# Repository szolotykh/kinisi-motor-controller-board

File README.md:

# Kinisi Motor Controller
For the current **v0.4** hardware, pin mappings, electrical limits and firmware compatibility, see [README_V4.md](README_V4.md). The overview below describes earlier revisions; interface counts and pin assignments differ.

For repeatable Gerber, drill, BOM and placement exports, see
[Regenerating a production package](README_V4.md#regenerating-a-production-package).

Kinisi motor controller is based on STM32F405 microcontroller controller. The controller can control up to 4 brushed DC motors with encoders. It offers platform obstruction which is means user doesn’t need to control each individual motor form main computer, but rather it can control up to four motors as a whole by sending high level commands like set target speed or distance for a platform.

Features:
* Controls 4 motors
* Receives readings from 4 encoders
* Supports encoders with wide range of supply voltage (3.3V, 5V, custom) 

Interfaces:
* USB Serial device
* I2C
* CAN
* 4x GPIO

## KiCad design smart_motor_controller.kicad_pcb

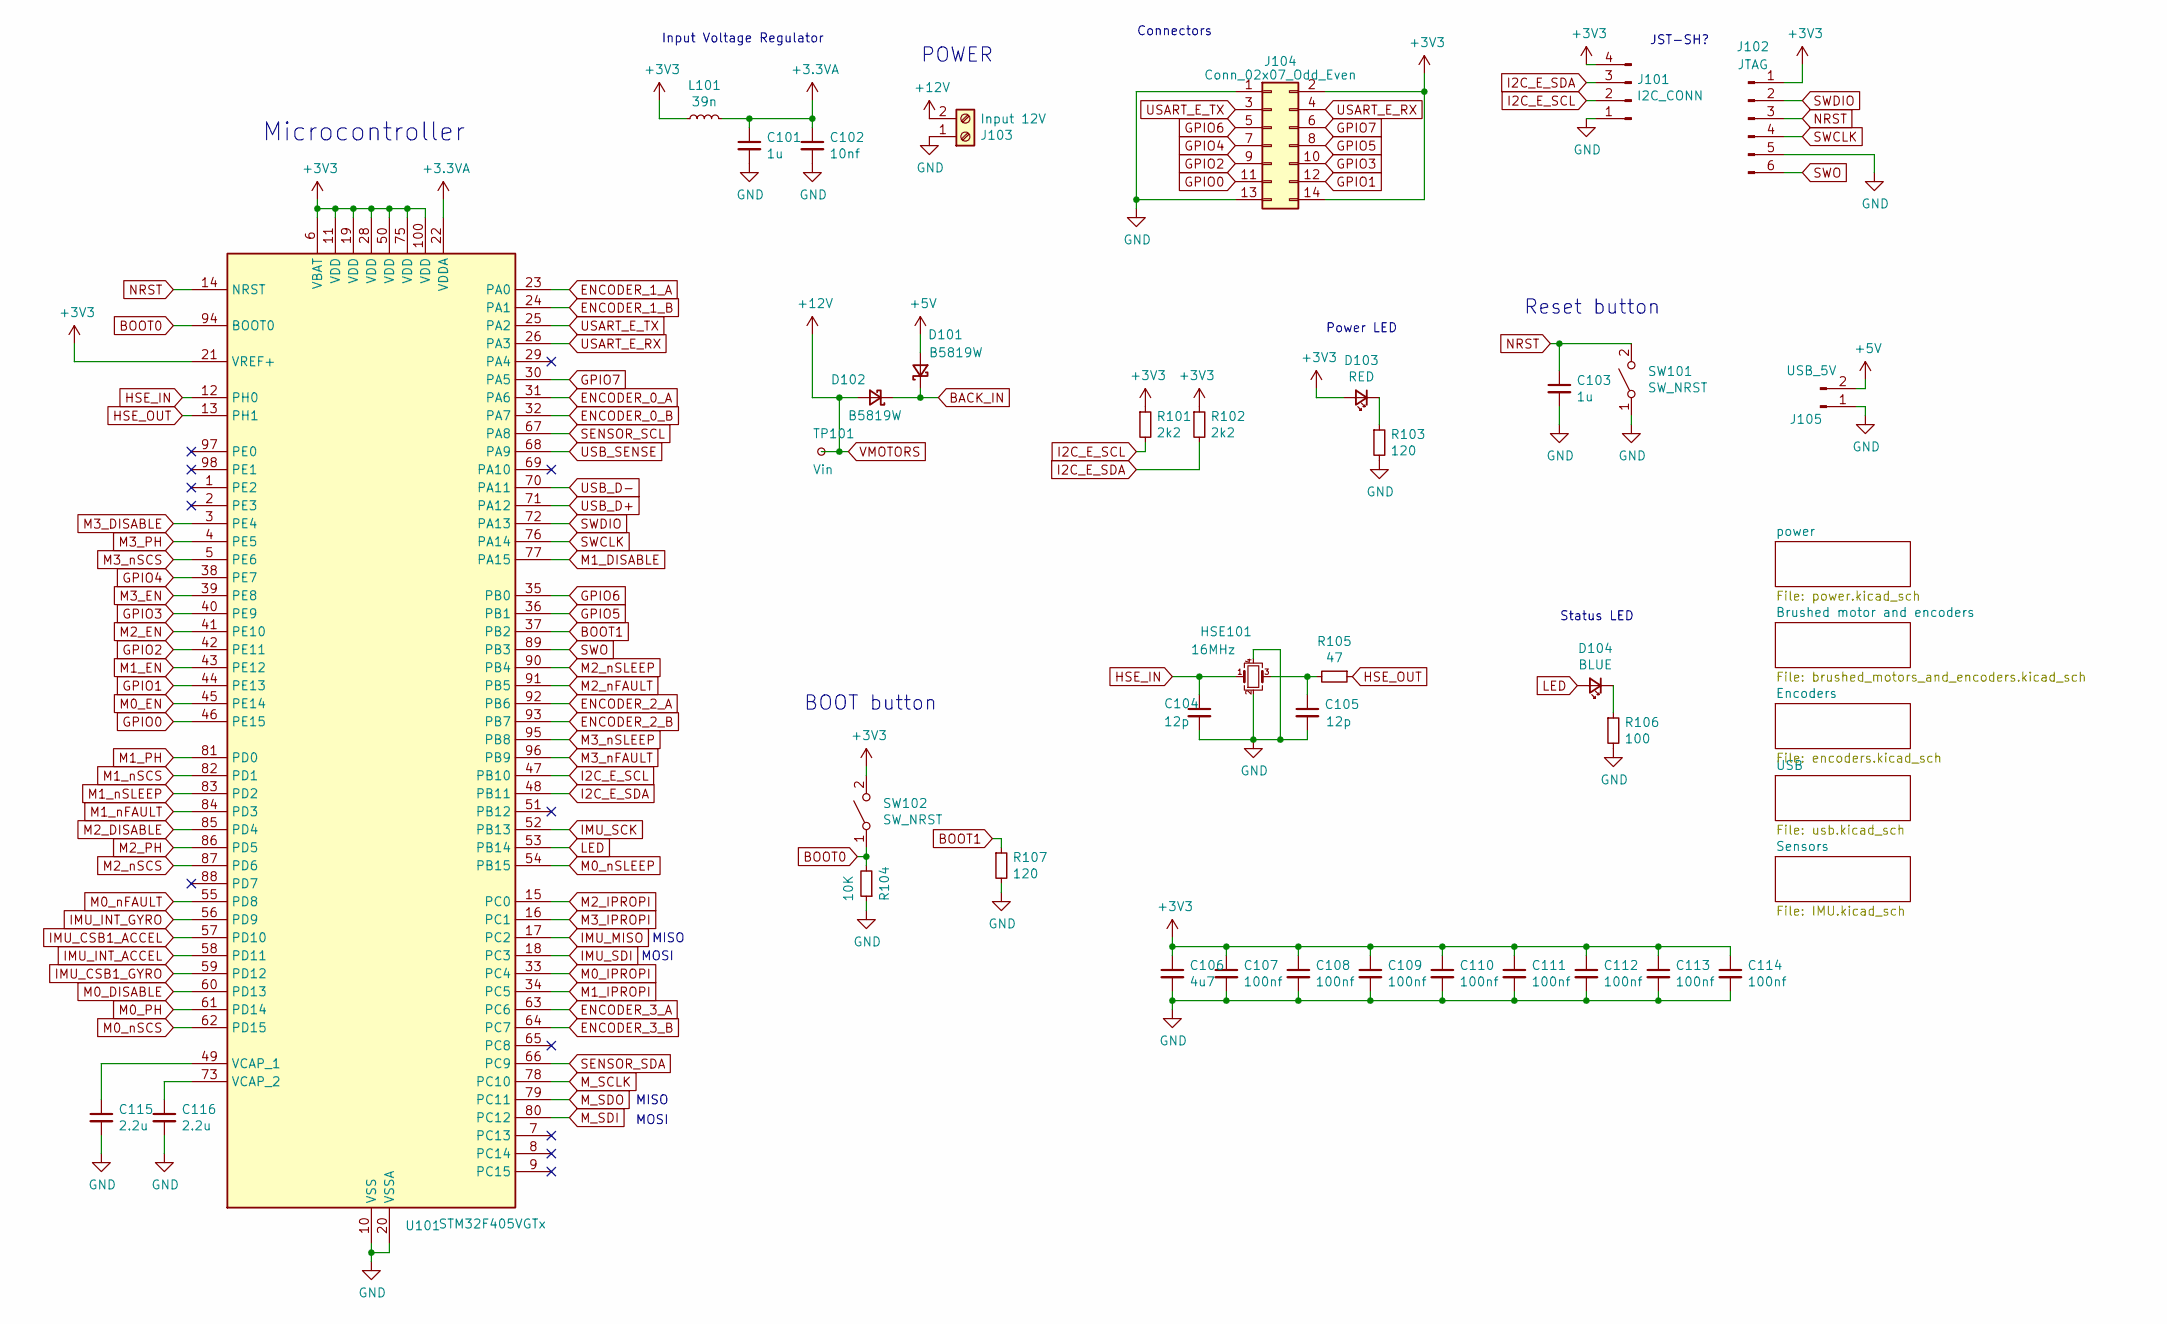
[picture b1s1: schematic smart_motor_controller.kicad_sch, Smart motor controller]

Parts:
C101, C103: 1u; C_0603_1608Metric; LCSC Part # C15849
C102: 10nf; C_0603_1608Metric; LCSC Part # C57112
C104, C105: 12p; C_0603_1608Metric; LCSC Part # C1642
C106: 4u7; C_0603_1608Metric; LCSC Part # C19666
C107, C108, C109, C110, C111, C112, C113, C114: 100nf; C_0603_1608Metric; LCSC Part # C694249
C115, C116: 2.2u; C_0603_1608Metric; LCSC Part # C23630
D101, D102: B5819W; D_SOD-123; LCSC Part # C8598
D103: RED; LED_0603_1608Metric; LCSC Part # C84263
D104: BLUE; LED_0603_1608Metric; LCSC Part # C193191
HSE101: 16MHz; Crystal_SMD_3225-4Pin_3.2x2.5mm; LCSC Part # C13738
J101: I2C_CONN; JST_PH_B4B-PH-K_1x04_P2.00mm_Vertical
J102: JTAG; Tag-Connect_TC2030-IDC-NL_2x03_P1.27mm_Vertical
J103: Input 12V; AMASS_XT30UPB-M_1x02_P5.0mm_Vertical
J104: Conn_02x07_Odd_Even; PinHeader_2x07_P2.54mm_Vertical
J105: USB_5V; PinHeader_2x01_P2.54mm_Vertical
L101: 39n; L_0603_1608Metric; LCSC Part # C964035
R101, R102: 2k2; R_0603_1608Metric; LCSC Part # C4190
R103, R107: 120; R_0603_1608Metric; LCSC Part # C22787
R104: 10K; R_0603_1608Metric; LCSC Part # C116677
R105: 47; R_0603_1608Metric; LCSC Part # C1211
R106: 100; R_0603_1608Metric; LCSC Part # C22775
SW101, SW102: SW_NRST; Diptronics MPTFP2-V-TR SMD 2.9x3.9x2mm; Part Evaluation C495942 is the specified SMD reset swit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; LCSC Part # C495942
TP101: Vin; TestPoint_Pad_D1.5mm
U101: STM32F405VGTx; LQFP-100_14x14mm_P0.5mm; Part Evaluation STM32F405VGT6 matches the STM32F405 dev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; LCSC Part # C56621

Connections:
+3.3VA: C101.1, C102.1, L101.2, U101.22 (VDDA)
+3V3: C106.1, C107.1, C108.1, C109.1, C110.1, C111.1, C112.1, C113.1, C114.1, D103.2 (A), J101.4, J102.1, J104.2, J104.14, L101.1, R101.1, R102.1, SW102.2 (B), U101.6 (VBAT), U101.11 (VDD), U101.19 (VDD), U101.21 (VREF+), U101.28 (VDD), U101.50 (VDD), U101.75 (VDD), U101.100 (VDD); also elsewhere on the board
+5V: D101.2 (A), J105.2; also elsewhere on the board
BACK_IN: D101.1 (K), D102.1 (K); also elsewhere on the board
BOOT0: R104.2, SW102.1 (A), U101.94 (BOOT0)
BOOT1: R107.1, U101.37 (PB2)
ENCODER_0_A: U101.31 (PA6); also elsewhere on the board
ENCODER_0_B: U101.32 (PA7); also elsewhere on the board
ENCODER_1_A: U101.23 (PA0); also elsewhere on the board
ENCODER_1_B: U101.24 (PA1); also elsewhere on the board
ENCODER_2_A: U101.92 (PB6); also elsewhere on the board
ENCODER_2_B: U101.93 (PB7); also elsewhere on the board
ENCODER_3_A: U101.63 (PC6); also elsewhere on the board
ENCODER_3_B: U101.64 (PC7); also elsewhere on the board
GND: C101.2, C102.2, C103.2, C104.2, C105.2, C106.2, C107.2, C108.2, C109.2, C110.2, C111.2, C112.2, C113.2, C114.2, C115.2, C116.2, HSE101.2, HSE101.4, J101.1, J102.5, J103.1, J104.1, J104.13, J105.1, R103.2, R104.1, R106.2, R107.2, SW101.1 (A), U101.10 (VSS), U101.20 (VSSA), U101.27 (VSS), U101.74 (VSS), U101.99 (VSS); also elsewhere on the board
GPIO0: J104.11, U101.46 (PE15)
GPIO1: J104.12, U101.44 (PE13)
GPIO2: J104.9, U101.42 (PE11)
GPIO3: J104.10, U101.40 (PE9)
GPIO4: J104.7, U101.38 (PE7)
GPIO5: J104.8, U101.36 (PB1)
GPIO6: J104.5, U101.35 (PB0)
GPIO7: J104.6, U101.30 (PA5)
HSE_IN: C104.1, HSE101.1, U101.12 (PH0)
HSE_OUT: R105.1, U101.13 (PH1)
I2C_E_SCL: J101.2, R101.2, U101.47 (PB10)
I2C_E_SDA: J101.3, R102.2, U101.48 (PB11)
IMU_CSB1_ACCEL: U101.57 (PD10); also elsewhere on the board
IMU_CSB1_GYRO: U101.59 (PD12); also elsewhere on the board
IMU_INT_ACCEL: U101.58 (PD11); also elsewhere on the board
IMU_INT_GYRO: U101.56 (PD9); also elsewhere on the board
IMU_MISO: U101.17 (PC2); also elsewhere on the board
IMU_SCK: U101.52 (PB13); also elsewhere on the board
IMU_SDI: U101.18 (PC3); also elsewhere on the board
LED: D104.2 (A), U101.53 (PB14)
M0_DISABLE: U101.60 (PD13); also elsewhere on the board
M0_EN: U101.45 (PE14); also elsewhere on the board
M0_IPROPI: U101.33 (PC4); also elsewhere on the board
M0_PH: U101.61 (PD14); also elsewhere on the board
M0_nFAULT: U101.55 (PD8); also elsewhere on the board
M0_nSCS: U101.62 (PD15); also elsewhere on the board
M0_nSLEEP: U101.54 (PB15); also elsewhere on the board
M1_DISABLE: U101.77 (PA15); also elsewhere on the board
M1_EN: U101.43 (PE12); also elsewhere on the board
M1_IPROPI: U101.34 (PC5); also elsewhere on the board
M1_PH: U101.81 (PD0); also elsewhere on the board
M1_nFAULT: U101.84 (PD3); also elsewhere on the board
M1_nSCS: U101.82 (PD1); also elsewhere on the board
M1_nSLEEP: U101.83 (PD2); also elsewhere on the board
M2_DISABLE: U101.85 (PD4); also elsewhere on the board
M2_EN: U101.41 (PE10); also elsewhere on the board
M2_IPROPI: U101.15 (PC0); also elsewhere on the board
M2_PH: U101.86 (PD5); also elsewhere on the board
M2_nFAULT: U101.91 (PB5); also elsewhere on the board
M2_nSCS: U101.87 (PD6); also elsewhere on the board
M2_nSLEEP: U101.90 (PB4); also elsewhere on the board
M3_DISABLE: U101.3 (PE4); also elsewhere on the board
M3_EN: U101.39 (PE8); also elsewhere on the board
M3_IPROPI: U101.16 (PC1); also elsewhere on the board
M3_PH: U101.4 (PE5); also elsewhere on the board
M3_nFAULT: U101.96 (PB9); also elsewhere on the board
M3_nSCS: U101.5 (PE6); also elsewhere on the board
M3_nSLEEP: U101.95 (PB8); also elsewhere on the board
M_SCLK: U101.78 (PC10); also elsewhere on the board
M_SDI: U101.80 (PC12); also elsewhere on the board
M_SDO: U101.79 (PC11); also elsewhere on the board
NRST: C103.1, J102.3, SW101.2 (B), U101.14 (NRST)
unnamed: C105.1, HSE101.3, R105.2
unnamed: D103.1 (K), R103.1
unnamed: D104.1 (K), R106.1
unnamed: C115.1, U101.49 (VCAP_1)
unnamed: C116.1, U101.73 (VCAP_2)
SENSOR_SCL: U101.67 (PA8); also elsewhere on the board
SENSOR_SDA: U101.66 (PC9); also elsewhere on the board
SWCLK: J102.4, U101.76 (PA14)
SWDIO: J102.2, U101.72 (PA13)
SWO: J102.6, U101.89 (PB3)
USART_E_RX: J104.4, U101.26 (PA3)
USART_E_TX: J104.3, U101.25 (PA2)
USB_D+: U101.71 (PA12); also elsewhere on the board
USB_D-: U101.70 (PA11); also elsewhere on the board
USB_SENSE: U101.68 (PA9); also elsewhere on the board
VMOTORS: D102.2 (A), J103.2, TP101.1 (1_1); also elsewhere on the board

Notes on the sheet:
MISO
Reset button
Input Voltage Regulator
Status LED
POWER
BOOT button
MOSI
Connectors
Power LED
JST-SH?
Microcontroller

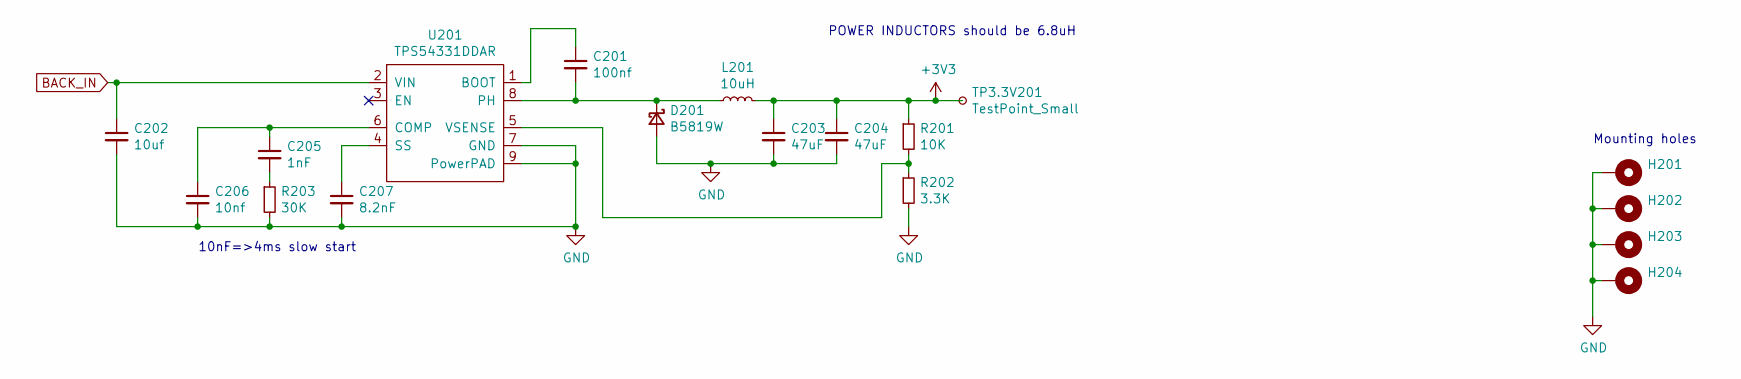
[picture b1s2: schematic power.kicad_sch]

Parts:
C201: 100nf; C_0603_1608Metric; LCSC Part # C694249
C202: 10uf; C_1206_3216Metric; LCSC Part # C13585
C203, C204: 47uF; C_0603_1608Metric; LCSC Part # C140782
C205: 1nF; C_0603_1608Metric; LCSC Part # C340644
C206: 10nf; C_0603_1608Metric; LCSC Part # C57112
C207: 8.2nF; C_0603_1608Metric; LCSC Part # C1322360
D201: B5819W; D_SOD-123; LCSC Part # C8598
H201, H202, H203, H204: MountingHole_Pad; MountingHole_3.2mm_M3_DIN965_Pad
L201: 10uH; L_Sunlord_MWSA0518_5.4x5.2mm; LCSC Part # C351099
R201: 10K; R_0603_1608Metric; LCSC Part # C116677
R202: 3.3K; R_0603_1608Metric; LCSC Part # C269710
R203: 30K; R_0603_1608Metric; LCSC Part # C22984
TP3.3V201: TestPoint_Small; TestPoint_Pad_D1.5mm
U201: TPS54331DDAR; HSOP-8-1EP_3.9x4.9mm_P1.27mm_EP2.41x3.1mm_ThermalVias; LCSC Part # C90761

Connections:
+3V3: C203.1, C204.1, L201.2, R201.1, TP3.3V201.1 (1_1); also elsewhere on the board
BACK_IN: C202.1, U201.2 (VIN); also elsewhere on the board
GND: C202.2, C203.2, C204.2, C206.2, C207.2, D201.2 (A), H201.1 (1_1), H202.1 (1_1), H203.1 (1_1), H204.1 (1_1), R202.2, R203.2, U201.7 (GND), U201.9 (PowerPAD); also elsewhere on the board
unnamed: C205.2, R203.1
unnamed: C201.2, D201.1 (K), L201.1, U201.8 (PH)
unnamed: C201.1, U201.1 (BOOT)
unnamed: C205.1, C206.1, U201.6 (COMP)
unnamed: C207.1, U201.4 (SS)
unnamed: R201.2, R202.1, U201.5 (VSENSE)

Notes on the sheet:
Mounting holes
POWER INDUCTORS should be 6.8uH
10nF=>4ms slow start

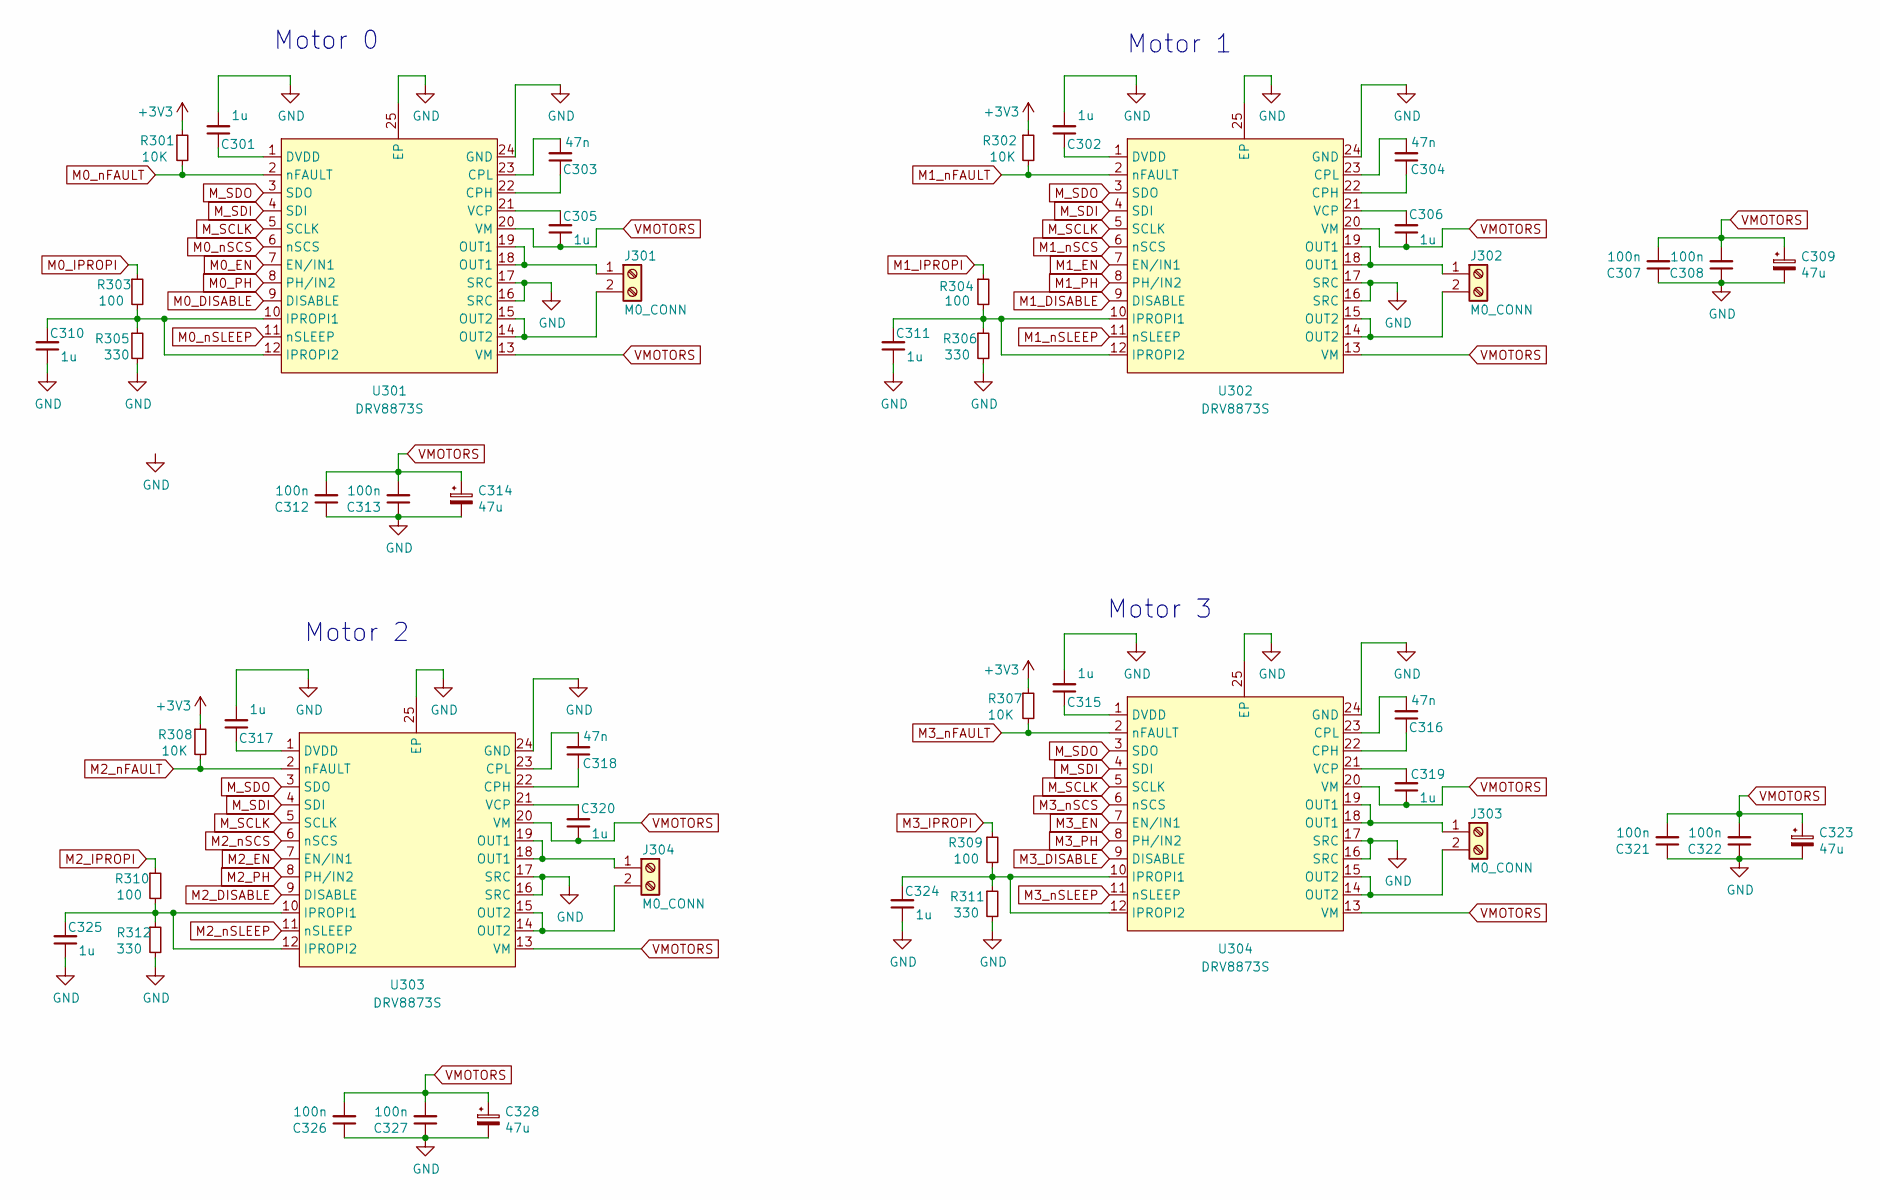
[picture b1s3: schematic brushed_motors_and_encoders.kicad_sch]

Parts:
C301, C302, C305, C306, C310, C311, C315, C317, C319, C320, C324, C325: 1u; C_0603_1608Metric; Part Evaluation 1uF, 50V X7R 0603 matches the required 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; LCSC Part # C90540
C303, C304, C316, C318: 47n; C_0603_1608Metric; Part Evaluation 47nF, 50V X7R 0603 matches the required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; LCSC Part # C696860
C307, C308, C312, C313, C321, C322, C326, C327: 100n; C_0603_1608Metric; LCSC Part # C14663
C309, C314, C323, C328: 47u; CP_Elec_5x5.4; Part Evaluation 47uF, 35V SMD capacitor matches the PCB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; LCSC Part # C22387982
J301, J302, J303, J304: M0_CONN; Ningbo_Kangnex_Elec_WJ128V_5_0_2P
R301, R302, R307, R308: 10K; R_0603_1608Metric; Part Evaluation 10k ohm, 1% 0603 matches the schematic 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; LCSC Part # C25804
R303, R304, R309, R310: 100; R_0603_1608Metric; Part Evaluation 100 ohm, 1% 0603 matches the schematic 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; LCSC Part # C22775
R305, R306, R311, R312: 330; R_0603_1608Metric; Part Evaluation 330 ohm, 1% 0603 matches the schematic 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; LCSC Part # C23138
U301, U302, U303, U304: DRV8873S; HTSSOP-24_L7.8-W4.4-P0.65-LS6.4-TL-EP; LCSC Part # C2150662

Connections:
+3V3: R301.1, R302.1, R307.1, R308.1; also elsewhere on the board
GND: C301.2, C302.2, C307.1, C308.1, C309.2, C310.1, C311.1, C312.1, C313.1, C314.2, C315.2, C317.2, C321.1, C322.1, C323.2, C324.1, C325.1, C326.1, C327.1, C328.2, R305.2, R306.2, R311.2, R312.2, U301.16 (SRC), U301.17 (SRC), U301.24 (GND), U301.25 (EP), U302.16 (SRC), U302.17 (SRC), U302.24 (GND), U302.25 (EP), U303.16 (SRC), U303.17 (SRC), U303.24 (GND), U303.25 (EP), U304.16 (SRC), U304.17 (SRC), U304.24 (GND), U304.25 (EP); also elsewhere on the board
M0_DISABLE: U301.9 (DISABLE); also elsewhere on the board
M0_EN: U301.7 (EN/IN1); also elsewhere on the board
M0_IPROPI: R303.1; also elsewhere on the board
M0_PH: U301.8 (PH/IN2); also elsewhere on the board
M0_nFAULT: R301.2, U301.2 (nFAULT); also elsewhere on the board
M0_nSCS: U301.6 (nSCS); also elsewhere on the board
M0_nSLEEP: U301.11 (nSLEEP); also elsewhere on the board
M1_DISABLE: U302.9 (DISABLE); also elsewhere on the board
M1_EN: U302.7 (EN/IN1); also elsewhere on the board
M1_IPROPI: R304.1; also elsewhere on the board
M1_PH: U302.8 (PH/IN2); also elsewhere on the board
M1_nFAULT: R302.2, U302.2 (nFAULT); also elsewhere on the board
M1_nSCS: U302.6 (nSCS); also elsewhere on the board
M1_nSLEEP: U302.11 (nSLEEP); also elsewhere on the board
M2_DISABLE: U303.9 (DISABLE); also elsewhere on the board
M2_EN: U303.7 (EN/IN1); also elsewhere on the board
M2_IPROPI: R310.1; also elsewhere on the board
M2_PH: U303.8 (PH/IN2); also elsewhere on the board
M2_nFAULT: R308.2, U303.2 (nFAULT); also elsewhere on the board
M2_nSCS: U303.6 (nSCS); also elsewhere on the board
M2_nSLEEP: U303.11 (nSLEEP); also elsewhere on the board
M3_DISABLE: U304.9 (DISABLE); also elsewhere on the board
M3_EN: U304.7 (EN/IN1); also elsewhere on the board
M3_IPROPI: R309.1; also elsewhere on the board
M3_PH: U304.8 (PH/IN2); also elsewhere on the board
M3_nFAULT: R307.2, U304.2 (nFAULT); also elsewhere on the board
M3_nSCS: U304.6 (nSCS); also elsewhere on the board
M3_nSLEEP: U304.11 (nSLEEP); also elsewhere on the board
M_SCLK: U301.5 (SCLK), U302.5 (SCLK), U303.5 (SCLK), U304.5 (SCLK); also elsewhere on the board
M_SDI: U301.4 (SDI), U302.4 (SDI), U303.4 (SDI), U304.4 (SDI); also elsewhere on the board
M_SDO: U301.3 (SDO), U302.3 (SDO), U303.3 (SDO), U304.3 (SDO); also elsewhere on the board
unnamed: J301.1, U301.18 (OUT1), U301.19 (OUT1)
unnamed: J301.2, U301.14 (OUT2), U301.15 (OUT2)
unnamed: J302.1, U302.18 (OUT1), U302.19 (OUT1)
unnamed: J302.2, U302.14 (OUT2), U302.15 (OUT2)
unnamed: J303.1, U304.18 (OUT1), U304.19 (OUT1)
unnamed: J303.2, U304.14 (OUT2), U304.15 (OUT2)
unnamed: J304.1, U303.18 (OUT1), U303.19 (OUT1)
unnamed: J304.2, U303.14 (OUT2), U303.15 (OUT2)
unnamed: C303.1, U301.22 (CPH)
unnamed: C303.2, U301.23 (CPL)
unnamed: C301.1, U301.1 (DVDD)
unnamed: C310.2, R303.2, R305.1, U301.10 (IPROPI1), U301.12 (IPROPI2)
unnamed: C305.2, U301.21 (VCP)
unnamed: C304.1, U302.22 (CPH)
unnamed: C304.2, U302.23 (CPL)
unnamed: C302.1, U302.1 (DVDD)
unnamed: C311.2, R304.2, R306.1, U302.10 (IPROPI1), U302.12 (IPROPI2)
unnamed: C306.2, U302.21 (VCP)
unnamed: C318.1, U303.22 (CPH)
unnamed: C318.2, U303.23 (CPL)
unnamed: C317.1, U303.1 (DVDD)
unnamed: C325.2, R310.2, R312.1, U303.10 (IPROPI1), U303.12 (IPROPI2)
unnamed: C320.2, U303.21 (VCP)
unnamed: C316.1, U304.22 (CPH)
unnamed: C316.2, U304.23 (CPL)
unnamed: C315.1, U304.1 (DVDD)
unnamed: C324.2, R309.2, R311.1, U304.10 (IPROPI1), U304.12 (IPROPI2)
unnamed: C319.2, U304.21 (VCP)
VMOTORS: C305.1, C306.1, C307.2, C308.2, C309.1, C312.2, C313.2, C314.1, C319.1, C320.1, C321.2, C322.2, C323.1, C326.2, C327.2, C328.1, U301.13 (VM), U301.20 (VM), U302.13 (VM), U302.20 (VM), U303.13 (VM), U303.20 (VM), U304.13 (VM), U304.20 (VM); also elsewhere on the board

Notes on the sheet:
Motor 2
Motor 1
Motor 3
Motor 0

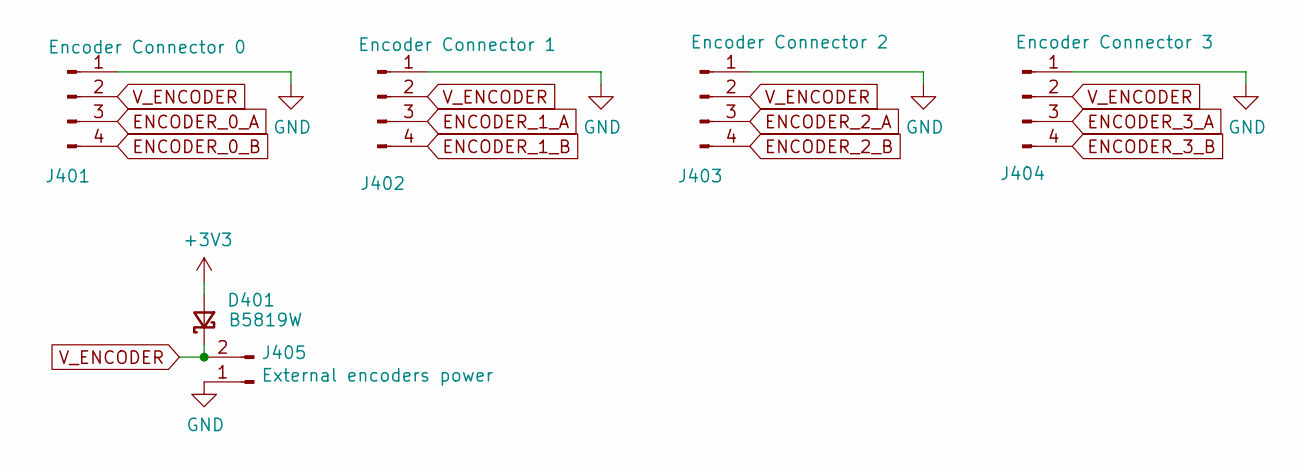
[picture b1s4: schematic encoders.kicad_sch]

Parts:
D401: B5819W; D_SOD-123_Encoder; LCSC Part # C8598
J401: Encoder Connector 0; JST_PH_B4B-PH-K_1x04_P2.00mm_Vertical
J402: Encoder Connector 1; JST_PH_B4B-PH-K_1x04_P2.00mm_Vertical
J403: Encoder Connector 2; JST_PH_B4B-PH-K_1x04_P2.00mm_Vertical
J404: Encoder Connector 3; JST_PH_B4B-PH-K_1x04_P2.00mm_Vertical
J405: External encoders power; PinHeader_1x02_P2.54mm_Vertical

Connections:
+3V3: D401.2 (A); also elsewhere on the board
ENCODER_0_A: J401.3; also elsewhere on the board
ENCODER_0_B: J401.4; also elsewhere on the board
ENCODER_1_A: J402.3; also elsewhere on the board
ENCODER_1_B: J402.4; also elsewhere on the board
ENCODER_2_A: J403.3; also elsewhere on the board
ENCODER_2_B: J403.4; also elsewhere on the board
ENCODER_3_A: J404.3; also elsewhere on the board
ENCODER_3_B: J404.4; also elsewhere on the board
GND: J401.1, J402.1, J403.1, J404.1, J405.1; also elsewhere on the board
V_ENCODER: D401.1 (K), J401.2, J402.2, J403.2, J404.2, J405.2

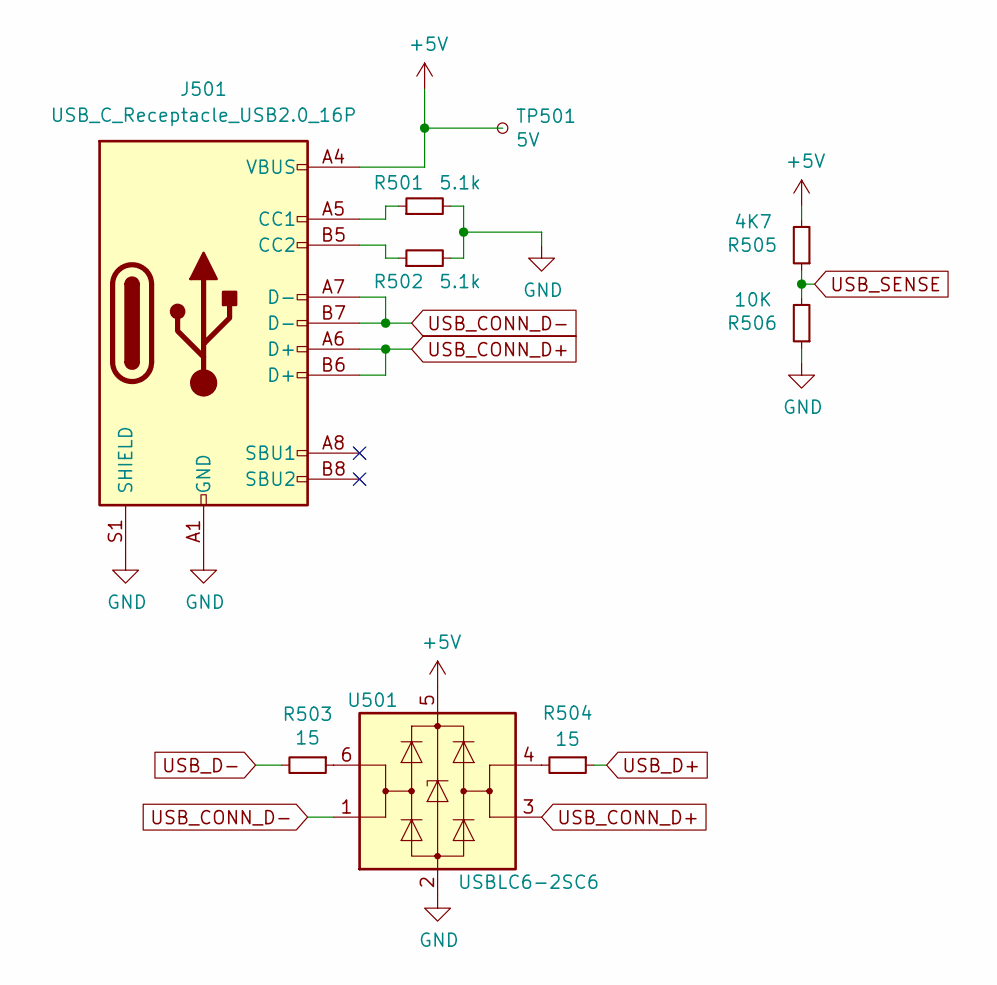
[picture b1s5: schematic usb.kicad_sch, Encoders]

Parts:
J501: USB_C_Receptacle_USB2.0_16P; USB_C_Receptacle_GCT_USB4105-xx-A_16P_TopMnt_Horizontal; Part Evaluation USB4105-GF-A-060 is the GCT USB-C recep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; LCSC Part # C3025063
R501, R502: 5.1k; R_0603_1608Metric; Part Evaluation 5.1k ohm, 1% 0603 matches the schematic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; LCSC Part # C23186
R503, R504: 15; R_0603_1608Metric; Part Evaluation 15 ohm, 1% 0603 (Uniroyal 0603WAF150JT5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; LCSC Part # C22810
R505: 4K7; R_0603_1608Metric; Part Evaluation 4.7k ohm, 1% 0603 matches the schematic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; LCSC Part # C23162
R506: 10K; R_0603_1608Metric; Part Evaluation 10k ohm, 1% 0603 matches the schematic 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; LCSC Part # C25804
TP501: 5V; TestPoint_Pad_D2.0mm
U501: USBLC6-2SC6; SOT-23-6; LCSC Part # C7519

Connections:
+5V: J501.A4 (VBUS), J501.A9 (VBUS), J501.B4 (VBUS), J501.B9 (VBUS), R505.2, TP501.1 (1_1), U501.5 (VBUS); also elsewhere on the board
GND: J501.A1 (GND), J501.A12 (GND), J501.B1 (GND), J501.B12 (GND), J501.S1 (SHIELD), R501.2, R502.2, R506.1, U501.2 (GND); also elsewhere on the board
unnamed: J501.A5 (CC1), R501.1
unnamed: J501.B5 (CC2), R502.1
unnamed: R503.1, U501.6 (I/O1)
unnamed: R504.2, U501.4 (I/O2)
USB_CONN_D+: J501.A6 (D+), J501.B6 (D+), U501.3 (I/O2)
USB_CONN_D-: J501.A7 (D-), J501.B7 (D-), U501.1 (I/O1)
USB_D+: R504.1; also elsewhere on the board
USB_D-: R503.2; also elsewhere on the board
USB_SENSE: R505.1, R506.2; also elsewhere on the board

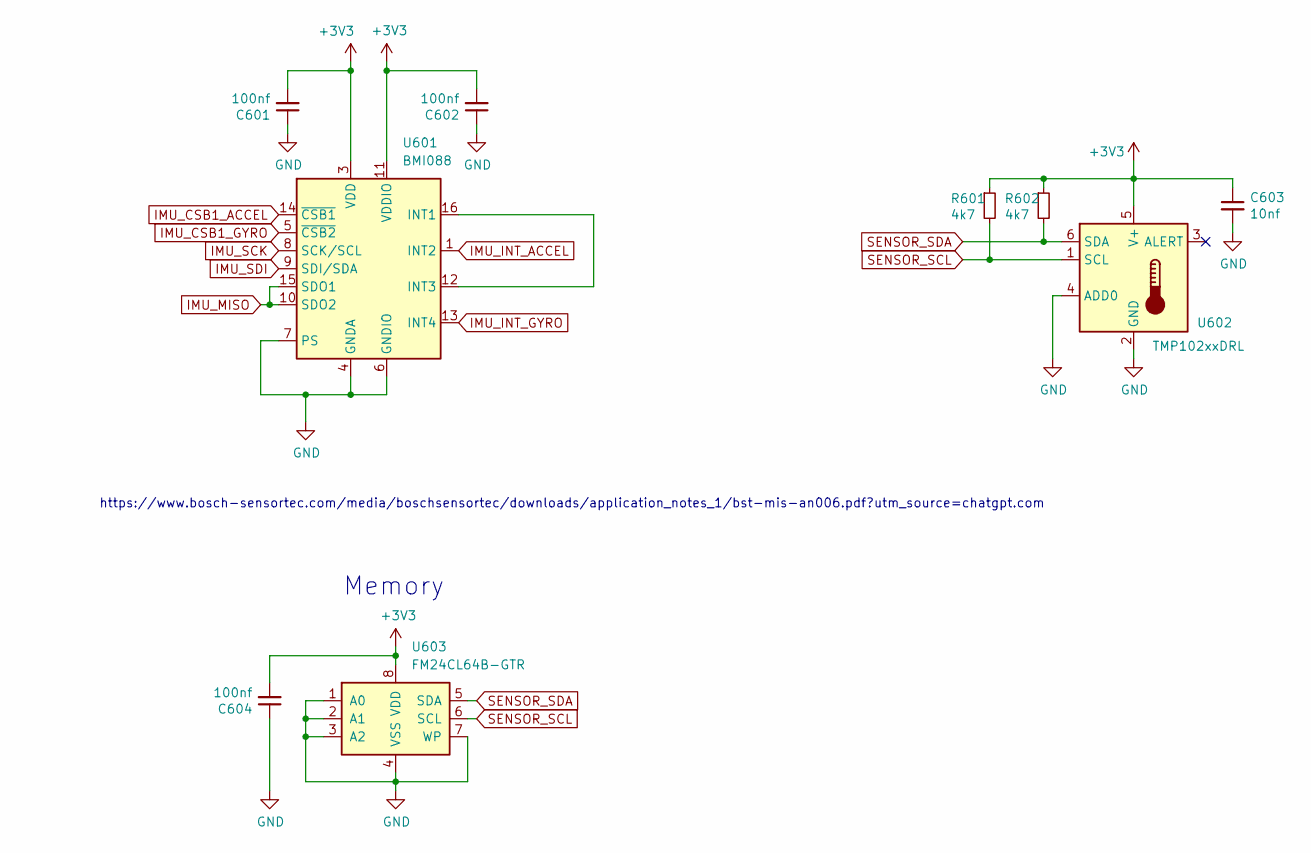
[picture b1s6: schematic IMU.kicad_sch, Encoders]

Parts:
C601, C602, C604: 100nf; C_0603_1608Metric; Part Evaluation 100nF, 50V X7R 0603 matches the decoupl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; LCSC Part # C14663
C603: 10nf; C_0603_1608Metric; LCSC Part # C57112
R601, R602: 4k7; R_0603_1608Metric; Part Evaluation 4.7k ohm, 1% 0603 matches the schematic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; LCSC Part # C23162
U601: BMI088; Bosch_LGA-16_4.5x3mm_P0.5mm_LayoutBorder7x1y_ClockwisePinNu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; Part Evaluation BMI088 matches the sensor symbol and ex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; LCSC Part # C194919
U602: TMP102xxDRL; SOT-563; Part Evaluation TMP102AIDRLR matches the temperature-se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; LCSC Part # C99269
U603: FM24CL64B-GTR; SOIC-8_3.9x4.9mm_P1.27mm; Part Evaluation FM24CL64B-GTR supports the board 3.3 V 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; LCSC Part # C9829

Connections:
+3V3: C601.2, C602.2, C603.1, C604.2, R601.1, R602.1, U601.3 (VDD), U601.11 (VDDIO), U602.5 (V+), U603.8 (VDD); also elsewhere on the board
GND: C601.1, C602.1, C603.2, C604.1, U601.2 (GNDA), U601.4 (GNDA), U601.6 (GNDIO), U601.7 (PS), U602.2 (GND), U602.4 (ADD0), U603.1 (A0), U603.2 (A1), U603.3 (A2), U603.4 (VSS), U603.7 (WP); also elsewhere on the board
IMU_CSB1_ACCEL: U601.14 (~CSB1); also elsewhere on the board
IMU_CSB1_GYRO: U601.5 (~CSB2); also elsewhere on the board
IMU_INT_ACCEL: U601.1 (INT2); also elsewhere on the board
IMU_INT_GYRO: U601.13 (INT4); also elsewhere on the board
IMU_MISO: U601.10 (SDO2), U601.15 (SDO1); also elsewhere on the board
IMU_SCK: U601.8 (SCK/SCL); also elsewhere on the board
IMU_SDI: U601.9 (SDI/SDA); also elsewhere on the board
unnamed: U601.12 (INT3), U601.16 (INT1)
SENSOR_SCL: R601.2, U602.1 (SCL), U603.6 (SCL); also elsewhere on the board
SENSOR_SDA: R602.2, U602.6 (SDA), U603.5 (SDA); also elsewhere on the board

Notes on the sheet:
Memory
https://www.bosch-sensortec.com/media/boschsensortec/downloads/application_notes_1/bst-mis-an006.pdf?utm_source=chatgpt.com
